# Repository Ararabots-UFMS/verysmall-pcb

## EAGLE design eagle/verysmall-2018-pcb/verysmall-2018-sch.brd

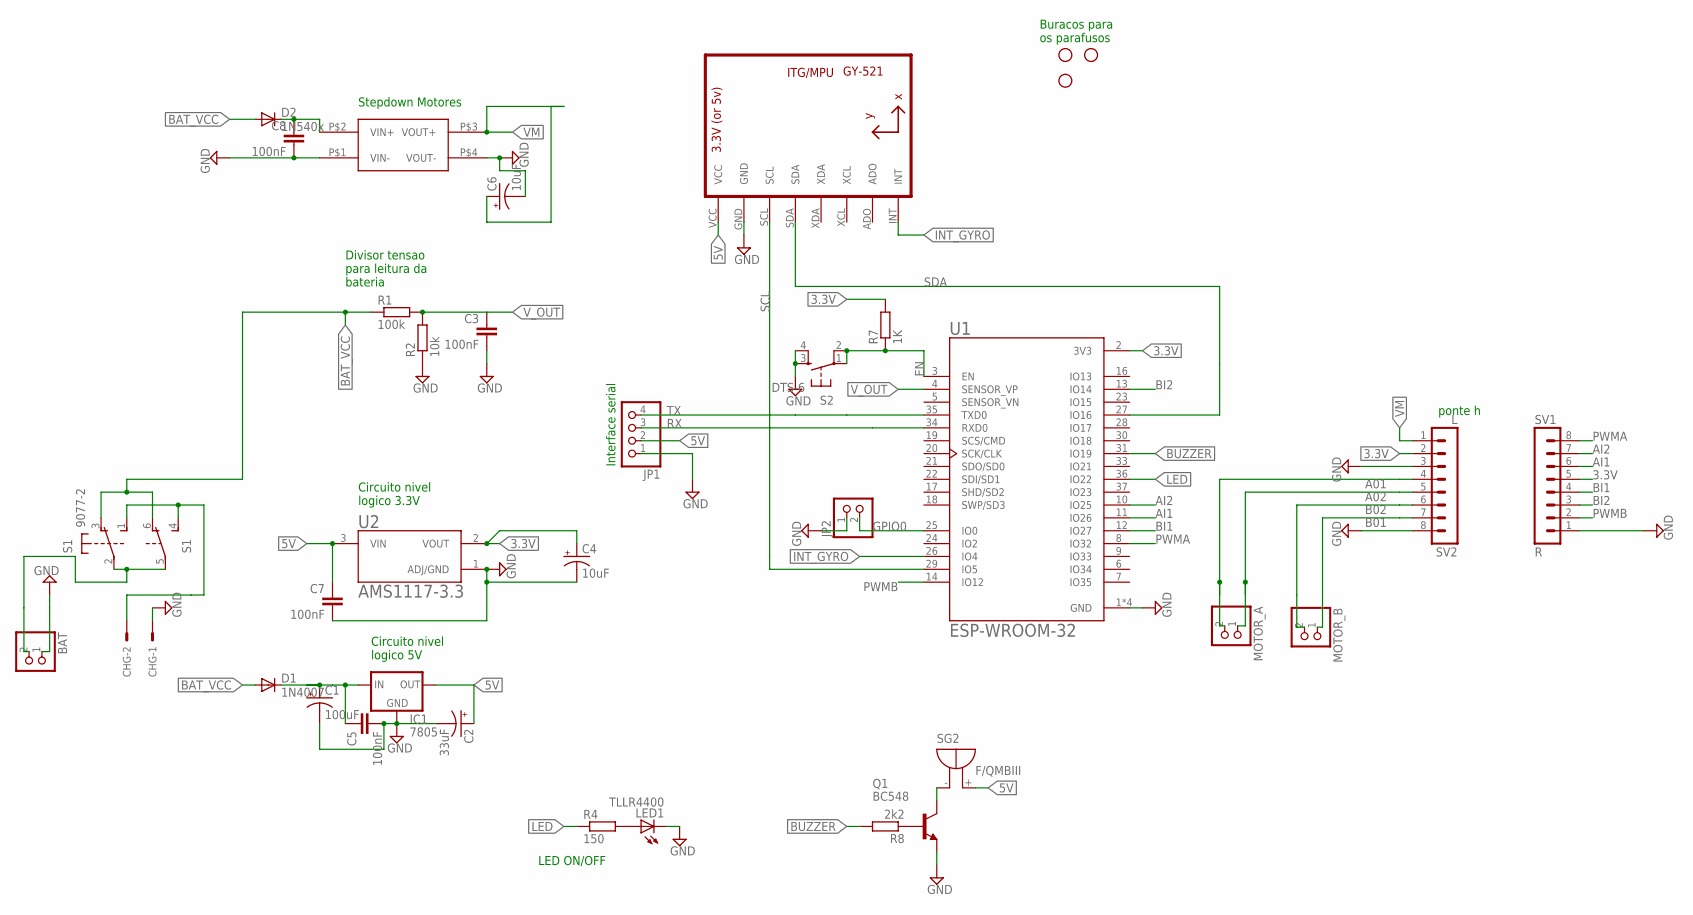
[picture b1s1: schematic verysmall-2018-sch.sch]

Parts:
BAT: PINHD-1X2; 1X02
C1: 100uF; E2-5
C2: 33uF; E2-5
C3, C5, C7, C8: 100nF; CAP-PTH-2.54
C4, C6: 10uF; E2-5
CHG: KK-156-2
D1: 1N4007; D-7.5
D2: 1N540x; DO201-15
H1, H2, H3: STAND-OFF
IC1: 7805; 78XXL
JP1: PINHD-1X4; 1X04
JP2: PINHD-1X2; 1X02
LED1: TLLR4400; LED3MM
MOTOR_A: PINHD-1X2; 1X02
MOTOR_B: PINHD-1X2; 1X02
Q1: BC548; TO92-EBC
R1: 100k; 0204/7
R2: 10k; 0204/7
R4: 150; 0207/7
R7: 1K; 0204/7
R8: 2k2; 0204/7
S1: 9077-2
S2: DTS-6
SG2: F/QMBIII
SV1: R; MA08-1
SV2: L; MA08-1
U1: ESP-WROOM-32; MODULE_ESP-WROOM-32
U2: AMS1117-3.3; SOT229P700X180-4N
U3: GY-521MPU6050; GY-521
U$1: MP1584-MINI-SMD; MINI-DC-BRICK-SMD

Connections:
3.3V: C4.+, R7.2, SV1.5, SV2.2, U1.2 (3V3), U2.2 (VOUT)
5V: C2.+, C7.1, IC1.OUT, JP1.2, SG2.+ (-), U2.3 (VIN), U3.VCC
A01: MOTOR_A.2, SV2.4
A02: MOTOR_A.1, SV2.5
AI1: SV1.6, U1.11 (IO26)
AI2: SV1.7, U1.10 (IO25)
B01: MOTOR_B.1, SV2.7
B02: MOTOR_B.2, SV2.6
BAT_VCC: D1.A, D2.A, R1.1, S1.3 (O), S1.6 (O)
BI1: SV1.4, U1.12 (IO27)
BI2: SV1.3, U1.13 (IO14)
BUZZER: R8.2, U1.31 (IO19)
EN: R7.1, S2.1, S2.2, U1.3 (EN)
GND: BAT.1, C1.-, C2.-, C3.2, C4.-, C5.2, C6.-, C7.2, C8.2, CHG.1, IC1.GND, JP1.1, JP2.1, LED1.K (C), Q1.E, R2.1, S2.3, S2.4, SV1.1, SV2.3, SV2.8, U1.1 (GND), U1.1.1 (GND), U1.15 (GND), U1.38 (GND), U2.1 (ADJ/GND), U3.GND, U$1.P$1 (VIN-), U$1.P$4 (VOUT-)
GPIO0: JP2.2, U1.25 (IO0)
INT_GYRO: U1.26 (IO4), U3.INT
LED: R4.1, U1.36 (IO22)
unnamed: C8.1, D2.C, U$1.P$2 (VIN+)
unnamed: LED1.A, R4.2
unnamed: CHG.2, S1.1 (S), S1.4 (S)
unnamed: BAT.2, S1.2, S1.5
unnamed: Q1.C, SG2.- (+)
unnamed: C1.+, C5.1, D1.C, IC1.IN
unnamed: Q1.B, R8.1
PWMA: SV1.8, U1.8 (IO32)
PWMB: SV1.2, U1.14 (IO12)
RX: JP1.3, U1.34 (RXD0)
SCL: U1.29 (IO5), U3.SCL
SDA: U1.27 (IO16), U3.SDA
TX: JP1.4, U1.35 (TXD0)
VM: C6.+, SV2.1, U$1.P$3 (VOUT+)
V_OUT: R1.2, R2.2, U1.4 (SENSOR_VP)

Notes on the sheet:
Divisor tensao para leitura da bateria
Circuito nivel logico 5V
Circuito nivel logico 3.3V
Stepdown Motores
ponte h
LED ON/OFF
Interface serial
Buracos para os parafusos

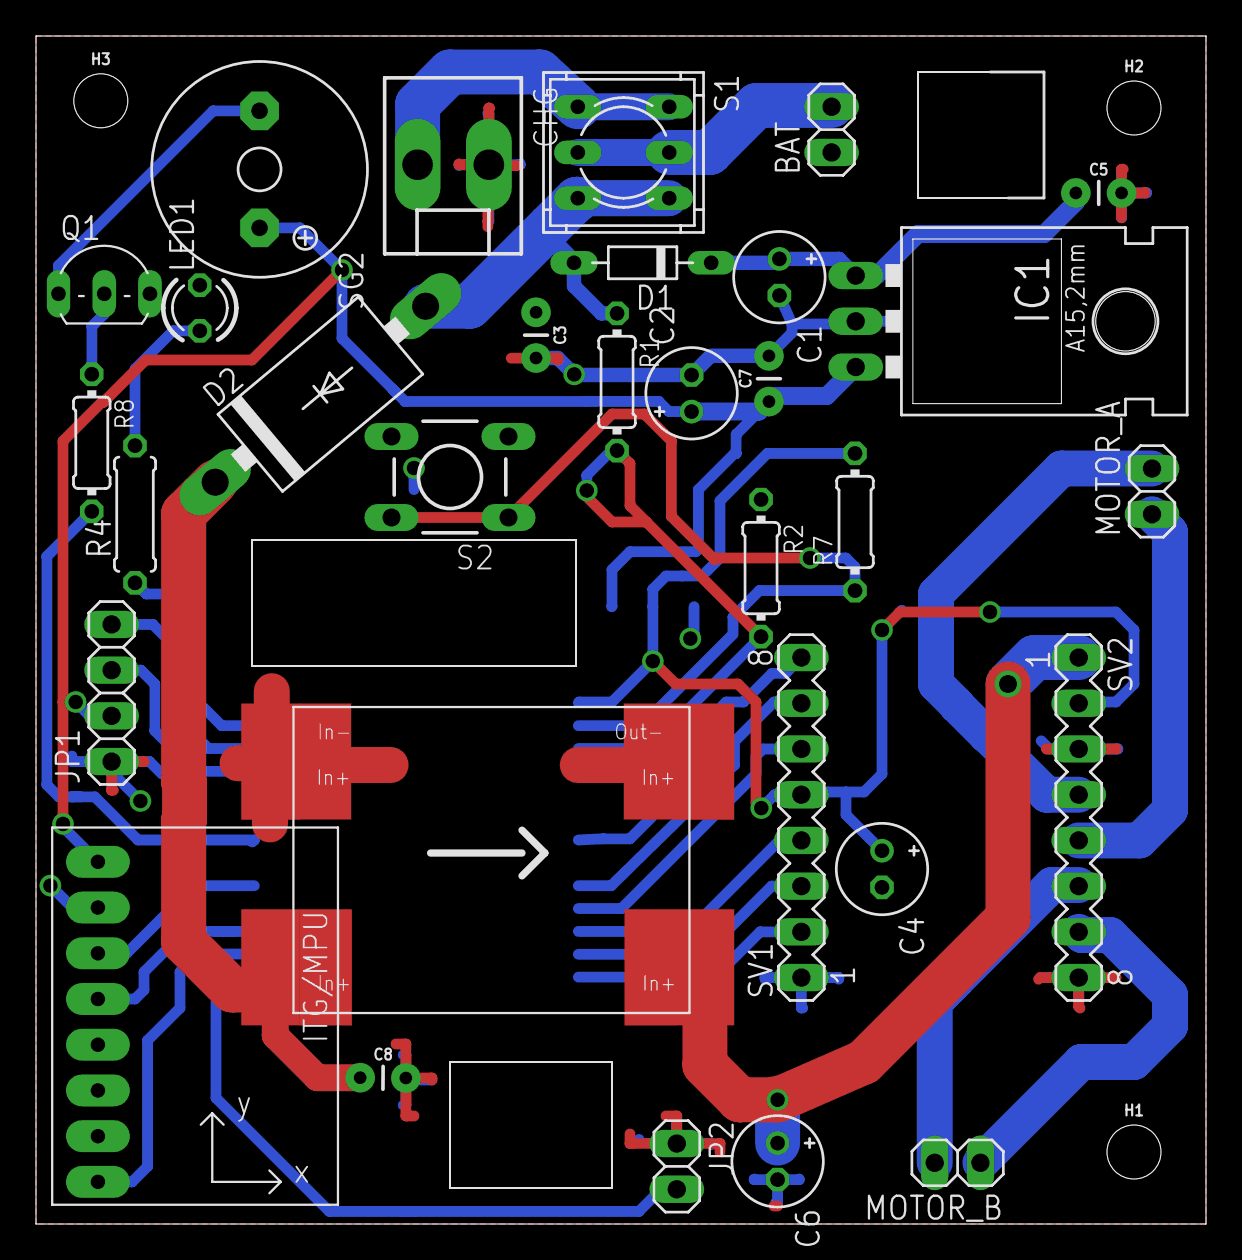
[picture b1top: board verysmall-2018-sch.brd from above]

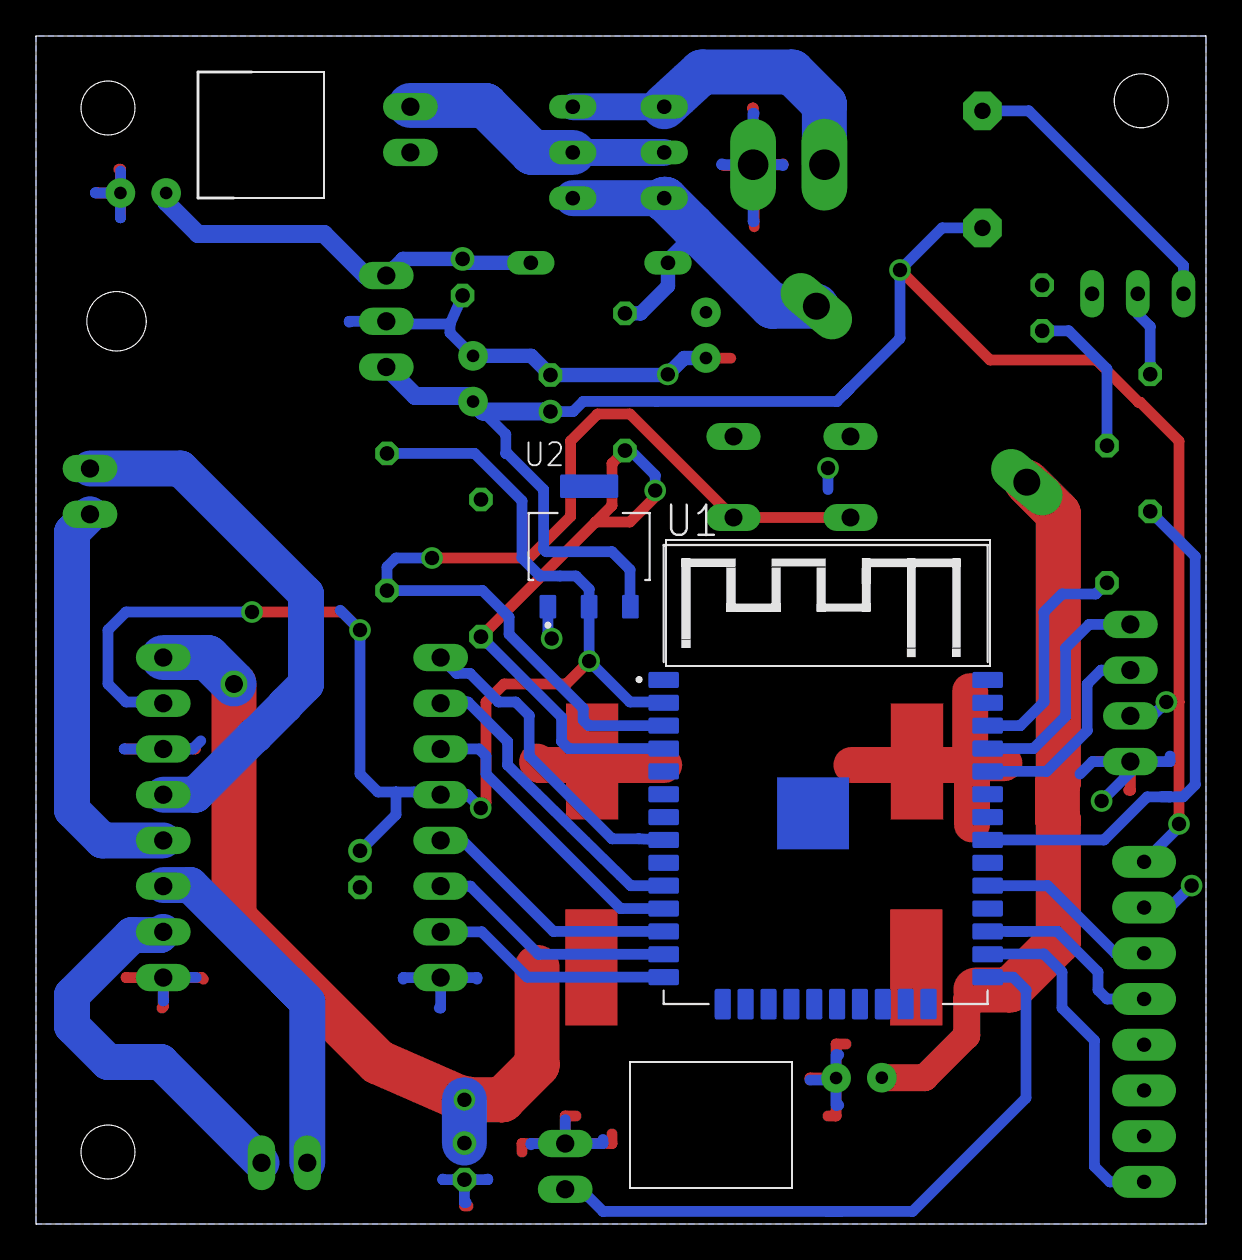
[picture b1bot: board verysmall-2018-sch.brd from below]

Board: 2 copper layers, 65.0 x 66.0 mm, 36 parts (2 on the bottom side), 32 nets.

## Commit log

2018-07-27 Adição do primeiro modelo de placa, necessário modificações.
2018-08-02 Ajuste na face do esp
2018-08-07 mudanças na dimensão da placa.
2018-08-08 corrigir gnd da ponte H
2018-08-11 eagle
2018-08-13 falta conferir pinagem ponte h
2018-08-13 falta conferir pinagem ponte h adicao led
2018-08-13 Adição dos pinos dos motores e do switch button
2018-08-18 Esquematico pronto
2018-08-18 Esquematico sem diodo
2018-08-19 ajuste de lable
2018-09-01 utlima versao plava
2018-10-12 atualizando
2019-09-24 deleting unnecessary files

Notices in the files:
parts and their libraries:
SparkFun-Capacitors: Licensing: Creative Commons ShareAlike 4.0 International - https://creativecommons.org/licenses/by-sa/4.0
